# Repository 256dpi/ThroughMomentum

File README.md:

# Through Momentum

**An interactive kinetic light installation.**

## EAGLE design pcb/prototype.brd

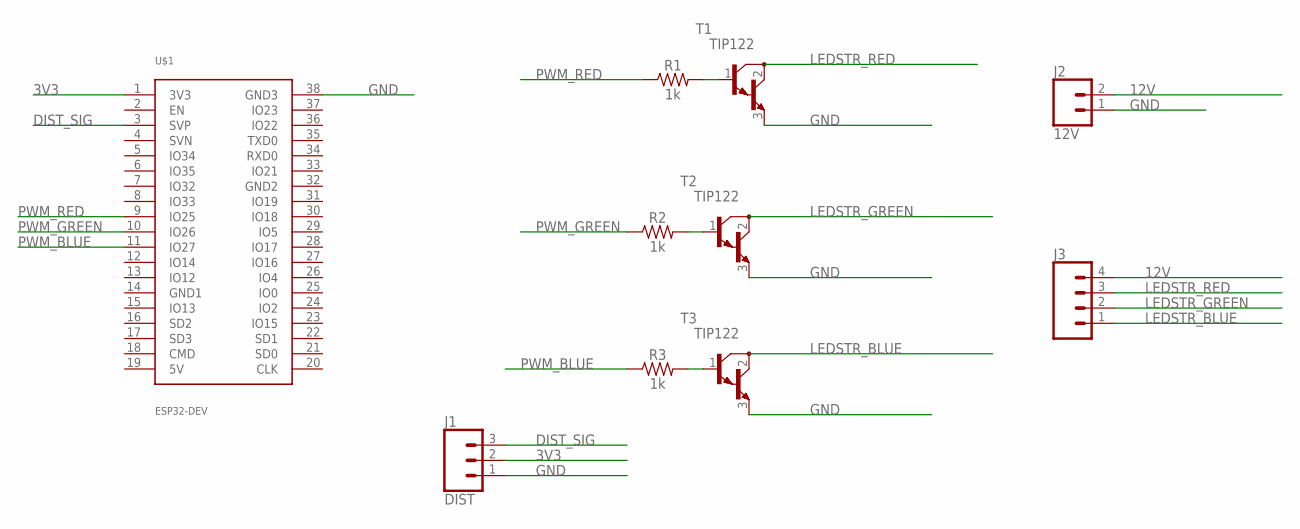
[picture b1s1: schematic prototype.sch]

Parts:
J1: DIST; 1X03_LONGPADS
J2: 12V; 1X02_LONGPADS
J3: CONN_04LONGPADS; 1X04_LONGPADS
R1, R2, R3: 1k; AXIAL-0.3
T1, T2, T3: TIP122; TO220
U$1: ESP32-DEV

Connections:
3V3: J1.2, U$1.1 (3V3)
12V: J2.2, J3.4
DIST_SIG: J1.3, U$1.3 (SVP)
GND: J1.1, J2.1, T1.3 (E), T2.3 (E), T3.3 (E), U$1.38 (GND3)
LEDSTR_BLUE: J3.1, T3.2 (C)
LEDSTR_GREEN: J3.2, T2.2 (C)
LEDSTR_RED: J3.3, T1.2 (C)
unnamed: R1.P$2 (2), T1.1 (B)
unnamed: R2.P$2 (2), T2.1 (B)
unnamed: R3.P$2 (2), T3.1 (B)
PWM_BLUE: R3.P$1 (1), U$1.11 (IO27)
PWM_GREEN: R2.P$1 (1), U$1.10 (IO26)
PWM_RED: R1.P$1 (1), U$1.9 (IO25)

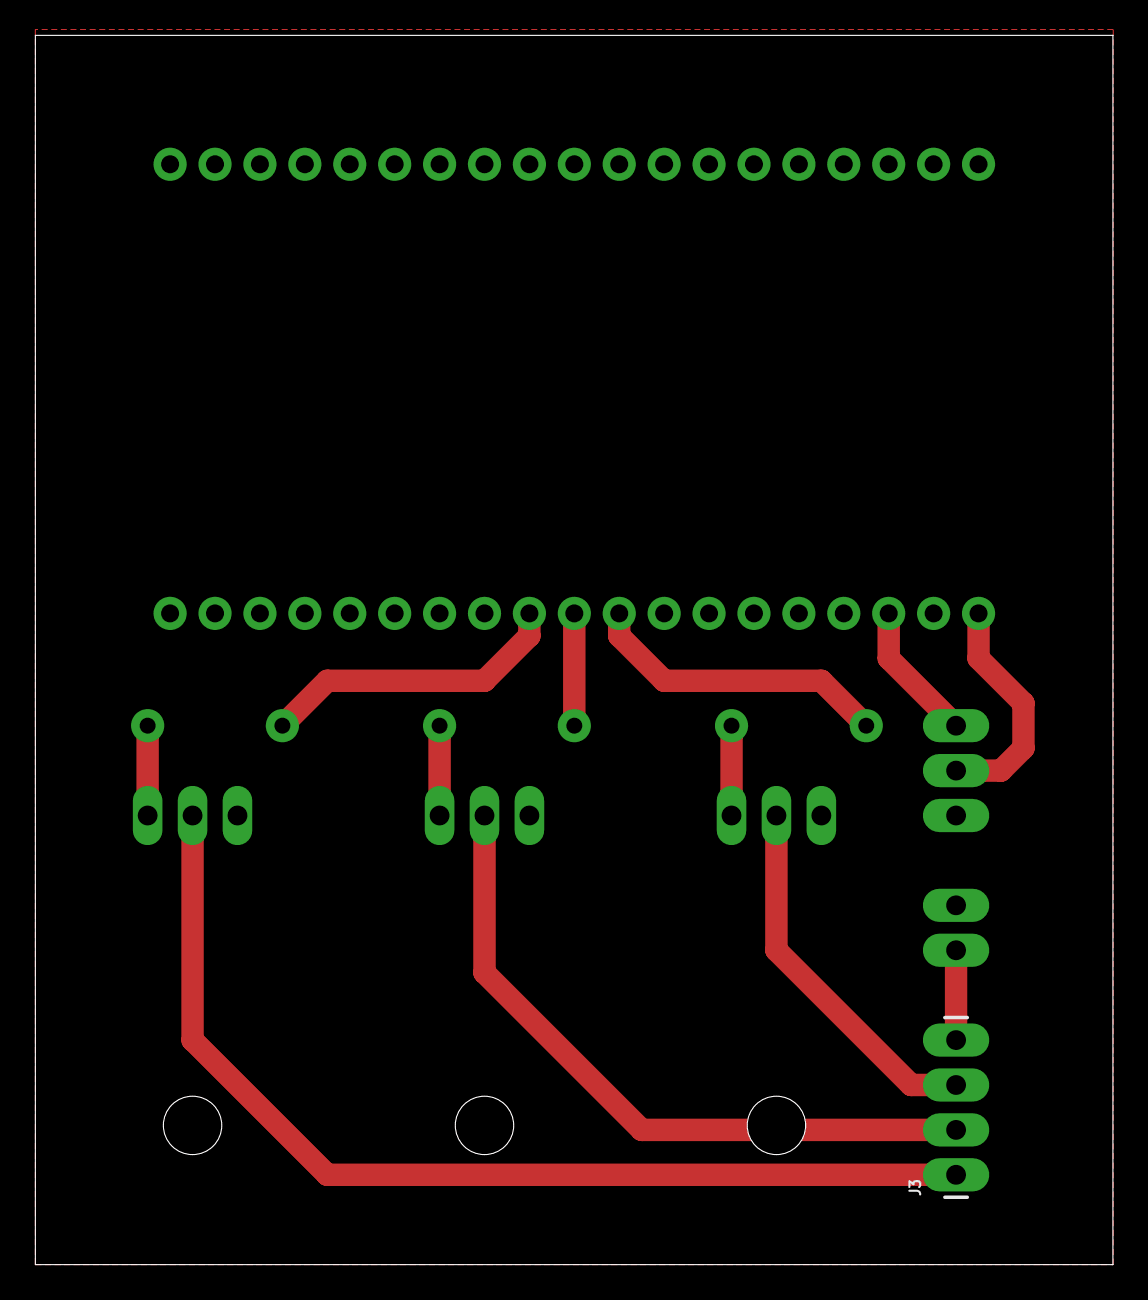
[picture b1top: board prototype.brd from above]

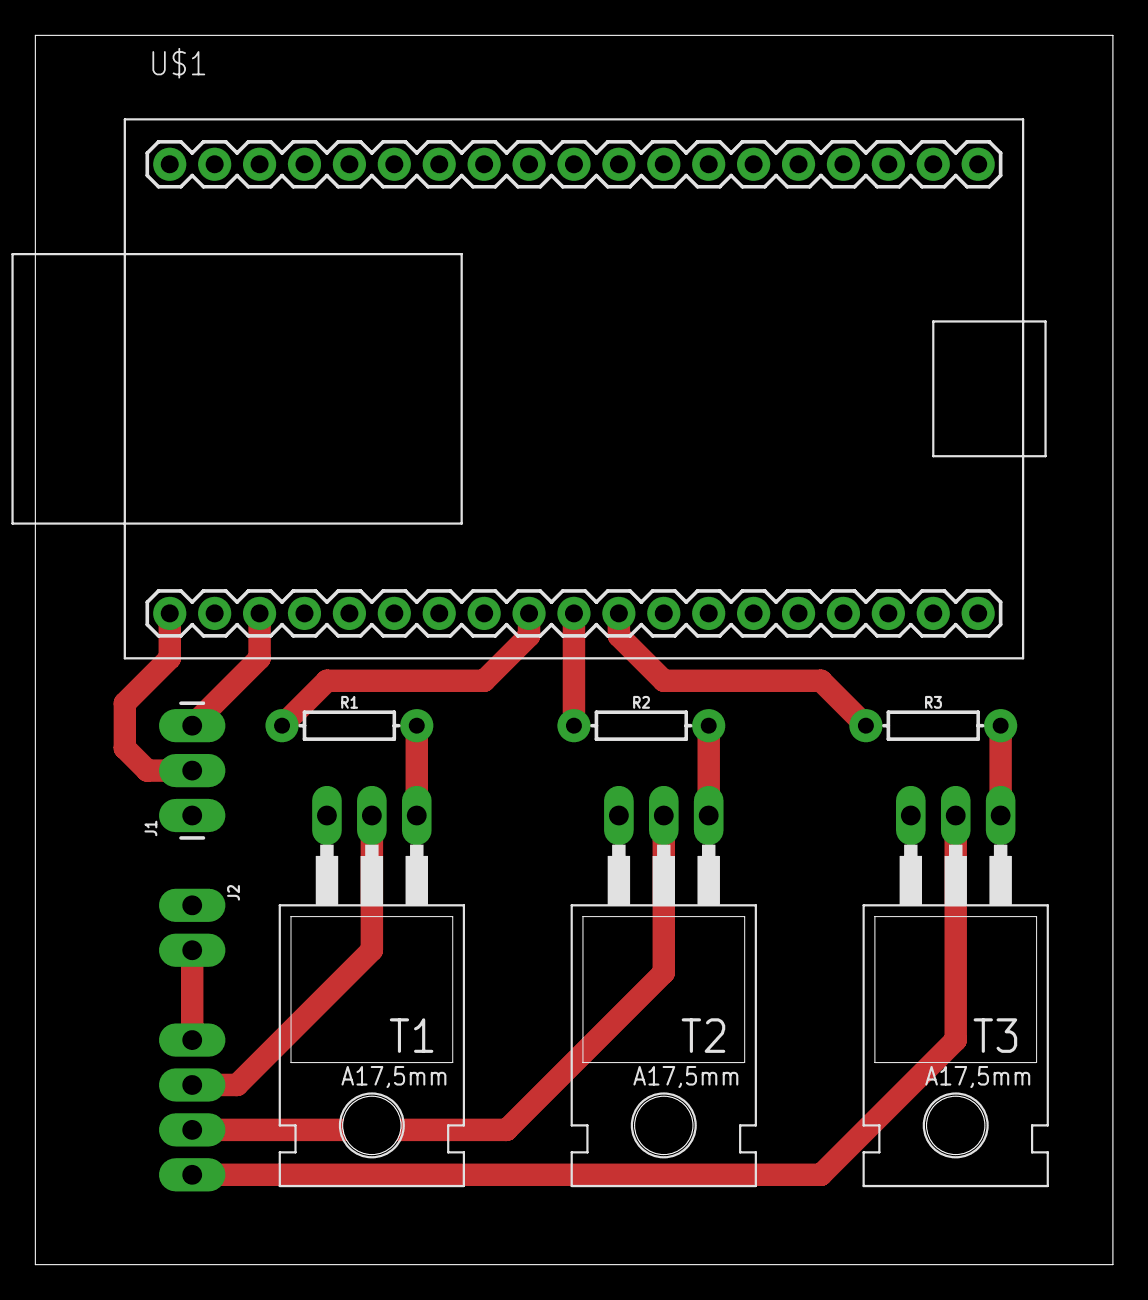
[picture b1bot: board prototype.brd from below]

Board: 2 copper layers, 60.9 x 69.5 mm, 10 parts (9 on the bottom side), 13 nets.

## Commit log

2017-07-13 removed audio and mic stuff
2017-07-13 collected device
2017-07-13 added processing sketch
2017-07-14 added prototype stuff
2017-09-17 removed old prototype stuff
2017-09-17 added pir and distance sensor readout
2017-09-17 use new time apis
2017-09-18 added motor
2017-09-18 basic motor control
2017-09-18 cleared up
2017-09-18 added todo
2017-09-18 added led control
2017-09-18 removed smoothing
2017-09-18 cleanup
2017-09-18 added sensor handling
2017-09-18 it does something, left to explore
2017-09-18 added encoder
2017-09-26 added pulse out module
2017-09-26 added experimental pulse in module
2017-09-26 use fade with motor
2017-09-26 already added
2017-09-26 format
2017-09-26 reflect new naos
2017-09-26 added global fade service
2017-09-26 added new motor control
2017-09-26 added new timer based distance measurement
2017-09-26 updated headers
2017-09-27 improved distance reading
2017-09-27 removed pulse modules
2017-09-28 use encoder to calculate target
2017-09-28 no ramp
2017-09-28 check scope
2017-09-28 fixed length
2017-09-28 fix target logging
2017-09-28 increase range
2017-09-28 fix dangling positions
2017-09-28 finish
2017-09-29 updated for new board
2017-09-29 make speed variable
2017-10-01 moved to firmware directory
2017-10-01 reflected changes
2017-10-01 added first interface version
2017-10-01 added display
2017-10-01 added carthage dependencies
2017-10-01 added mqtt
2017-10-01 finished interface
2017-10-01 updated colors
2017-10-01 added settings bundle
2017-10-01 not needed anymore
2017-10-01 added ping callback
2017-10-01 added comment
2017-10-01 just log target
2017-10-01 reset in module
2017-10-01 disables leds when offline
2017-10-01 added basic flash command
2017-10-01 added disco mode
2017-10-01 added idle light
2017-10-01 added stop command
2017-10-04 fixed orientation
2017-10-04 improved offline handling
2017-10-06 added note
2017-10-06 moved disco down
2017-10-06 invert motor direction
2017-10-06 implement automate as a naos setting
2017-10-06 added more parameters
2017-10-06 renamed to height
2017-10-06 clarify and document parameters
2017-10-06 encoder defines resolution
2017-10-06 added winding length parameter and defaults
2017-10-06 simplified
2017-10-06 added idle-light and flash-intensity
2017-10-06 added art32
2017-10-06 use art32 helpers
2017-10-06 simplify
2017-10-06 added automatic position saving
2017-10-06 compare exactly
2017-10-06 made speed a naos parameter
2017-10-06 added target distance parameter
2017-10-06 added ledc fade service
2017-10-06 publish distance every 1sec
2017-10-06 update motor and encoder
2017-10-06 added led fade
2017-10-06 init with saved position
2017-10-06 updated flash
2017-10-06 added turn and manual mode
2017-10-06 reflect changes
2017-10-06 calculate real target
2017-10-07 map max up and down speed
2017-10-07 added else keywords
2017-10-07 configurable min up and down speeds
2017-10-07 added else modifiers
2017-10-07 check automate first
2017-10-07 documented new parameters
2017-10-07 added speed-map-range parameter and updated default values
2017-10-07 added distance smoothing
2017-10-07 boostrapped the controller ap
2017-10-07 hide status bar during launch
2017-10-07 prepared app
2017-10-07 prepared circle component
2017-10-08 added basic circleview
2017-10-08 added preferences
2017-10-08 updated topics
2017-10-08 integrated mqtt
2017-10-08 integrated detail view controller
2017-10-08 added detail view recalculation
2017-10-08 connected the buttons
2017-10-08 pass data to detail view controller
2017-10-08 optimized data passing
2017-10-08 show a zero circe view
2017-10-08 finished move control
2017-10-08 increase max down speed
2017-10-08 added experimental pir mode
2017-10-08 added encoder inversion
2017-10-09 cleaned
2017-10-09 always set correct target
2017-10-09 added missing else
2017-10-09 added move precision parameter
2017-10-09 fix some led issues
2017-10-09 removed log
2017-10-09 use new pir access mode
2017-10-09 removed old pir api
2017-10-09 cleaned up
2017-10-09 added pir configuration
2017-10-10 updated interface to match firmware
2017-10-10 make led flash time configurable
2017-10-10 bumped version
2017-10-10 prepare config
2017-10-10 added move all buttons
2017-10-11 added crash on mqtt failures
2017-10-11 changed deployment target
2017-10-11 increased queue size to save quadrature for up to 2m
2017-10-11 only read position from flash on first boot
2017-10-11 fix zero target bug
2017-10-12 removed distance module for the moment
2017-10-12 added flash color
2017-10-12 got all devices
2017-10-12 set idle height
2017-10-12 set rise height
2017-10-12 set pir sensitivity
2017-10-12 set max up speed
2017-10-12 updated controller
2017-10-12 added color settings
2017-10-12 show color in interface
2017-10-12 reduced deployment target
2017-10-12 make client id configurable
2017-10-13 read max height
2017-10-13 removed unused max height
2017-10-14 implemented encoder without queues
2017-10-14 only update position if changed at least 1cm
2017-10-14 updated most devices
2017-10-14 added docs
2018-04-18 fix firmware
2018-04-19 use new params api for parameter handling
2018-04-19 reflect naos changes
2018-06-25 added end stop detector
2018-06-26 synchronize callback
2018-06-26 moved
2018-06-26 maker encoder async
2018-06-26 use new function
2018-06-26 make vars static
2018-06-26 fix deprecation
2018-06-26 removed position saving
2018-06-26 handle fade out in led module
2018-06-26 improved led fading
2018-06-26 added sections
2018-06-26 removed not needed callback
2018-06-26 extract approach target method
2018-06-26 refactored code as state machine
2018-06-26 updated parameters
2018-06-26 renamed actions
2018-06-26 removed reset
2018-06-26 moved file
2018-06-26 added mot_stop method
2018-06-26 use approach to move up and down
2018-06-26 use 5cm instead of 10
2018-06-26 added base height and constrain move to
2018-06-26 renamed buttons
2018-06-26 added zero handler
2018-06-26 added zero button
2018-06-26 fixed
2018-06-26 switched to cocoa pods
2018-06-26 publish states
2018-06-26 added configurable zero speed
2018-06-26 display state
2018-06-26 properly apply parameter changes
2018-06-26 fix controller
2018-06-27 added guard
2018-06-27 added back distance sensor
2018-06-28 added power supply firmware
2018-07-06 fixed up and down move and added zero switch
2018-07-19 added final firmware
2018-07-26 added ping callback and set initial relay state
2018-09-04 renamed project
2018-09-04 fix bug
2018-09-04 updated config
2018-09-05 renamed
2018-09-06 do only once
2018-09-07 make move up and move down speed configurable
2018-09-07 control motor movements with a motion profile
2018-09-07 improved positioning
2018-09-07 remove zero state and some parameters
2018-09-07 finished interaction
2018-09-24 use cocoapods
2018-09-25 added grid based layouting
2018-09-27 added color command
2018-09-27 fixed hk interface setup
2018-09-28 updated firmware
2018-09-28 updated interface
2018-09-28 small fixes
2018-09-28 added initialize state
2018-09-28 fix led fadinf
2018-09-28 implement disco in app
2018-09-28 small fix
2018-09-28 improved led again
2018-09-28 improved distance handling
2018-09-28 changed init order
2018-09-28 added async pir implementation
2018-09-28 removed winding length param
2018-09-29 updated docs
2018-09-29 added constants
2018-09-29 transition to initialize if not yet initialized
2018-09-29 stop motor when state is entered
2018-09-29 use distance for initial position
2018-09-29 fixed distance range
2018-09-29 reduce smoothing
2018-09-29 reduced range again
2018-09-29 added visual calibration using distance sensor
2018-09-29 represent states with colors
2018-09-29 bump version
2018-09-29 added api to read end switch
2018-09-29 disable automate if end switch is pressed on boot
2018-09-29 re-calibrate after some usage
2018-10-02 make calibration interval configurable
2018-10-02 added color cycling
2018-10-02 increased stack size for all tasks
2018-10-02 give some leeway for calibration
2018-10-03 added constants and only change color if state is ok
2018-10-03 added new parameters
2018-10-03 fixed controller view issues
2018-10-03 added debug parameter to control debug coloring
2018-10-03 finished controller
2018-10-03 renamed keys
2018-10-03 updated layout
2018-10-03 added color animation
2018-10-04 added password
2019-04-17 remove obsolete variable
2019-09-05 changed developer
2019-09-12 added port config

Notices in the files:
parts and their libraries:
SparkFun-Connectors: Licensing: Creative Commons ShareAlike 4.0 International - https://creativecommons.org/licenses/by-sa/4.0
